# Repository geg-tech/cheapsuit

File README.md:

# *CHEAP SUITS*
A custom Hacker Card in the profile and style of a Bicycle Playing Card.

 <br/>
 <br/>

I've had the idea of a Hack Club playing card for a *long while* (ever since my BakeBuild submission back in April), and with some extra time on my hands and inpsiration from other people submitting hacker cards, I decided to revamp this idea into a hacker card PCB with fully custom art! <br/>
*Featuring cool and shiny graphics! wow!*

this hacker card also doubles as a shameless plug to my insta account lmao

## PCB
### Schematic
 <br/>

### PCB 
 <br/>
 <br/>
 <br/>

## BOM
| part | quantity | price | purpose/name |
| --- | --- | --- | --- |
| 25X48MM_NFC_ANTENNA | 1 | $0.00 (copper layers)| receives power and transmits |
| CL10B224KA8NNNC | 1 | $0.0270 | Assists the power harvester system |
| E6C0805UR | 1 | $0.0050 | 47 ohm resistor to limit power leading to the LED | 
| KT-0805Y | 1 | $0.0625 | 2V red LED that lights up |
| | | |
| PCB | 5 | $2.00 | PCB that holds/wires components together |
| PCBA Total | idk | $15.12 | all the other stuff that comes with PCBA; setup fee, stencil, components, etc. (why is it so damn expensive 🥀) |
| Shipping: $9.97 | Tax: $1.79 | | |
|**Total: $28.85**| ($9.38 with the jlc coupon) | | |
> note: the actual PCBA BOM is located under the production folder

## Firmware
putting this here since the firmware is literally just flashing the NFC chip and uploading with an app <br/>
Command: `A2:03:E1:10:6D:00,A2:04:03:04:D8:00,A2:05:00:00:FE:00` <br/>
Purpose: Will link to my Instagram account (@hunk.egg btw :3)

## extras/inspirations

***fun facts***:
* I drew two alternate back sides to the playing card, being the *Moon* and the *Compass*!
* ^ The *Moon* was inspired off of the background of [Cheap Suits](https://youtu.be/87i0RargAcA) and traditional tarot cards
* ^^ The *Compass* had an original theming for being a *compass* for Highway (get it)

 <br/>

* This project initially had the name of *The Hack* in my head, being named after the Balatro joker of the same name and also matching with *Hack* Club
* ^ i then found out that this was not a poker/cards term, but instead is slang for cliche and unoriginal jokes
* I hid the logos for Highway and Undercity on the back side of the card, as well as the Hack Club flag :3

***inspirations***:
* **Cyberpunk 2077** - Main inspiration behind the cyberpunk/hardcore tech theming
* [**Cheap Suits**](https://youtu.be/87i0RargAcA) by *mekaloton* - Main inspiration for the whole suits/gambling theme; inspired the *Moon* alternate back side; this entire project was named after this song lmao
* **Balatro** - Also a main inspiration for the gambling/suits theme
* **Bicycle Playing Cards** - Main inspiration behind the chosen back side design
* **Highway/Undercity/Hack Club** - (oddly enough) The original source of the cyberpunk aesthetic I wanted with this card; inspired much of the art for the suits, the Undercitified Hack Club logo, and the Highway Stars
* [**Azimuth**](https://www.youtube.com/watch?v=hgSNrjHIIF0) by Knots (YES THIS IS A GEOMETRY DASH LEVEL 🙏😭) - Main inspiration behind the *Compass* alternate back side
* **my calculus teacher** - he got me addicted to poker

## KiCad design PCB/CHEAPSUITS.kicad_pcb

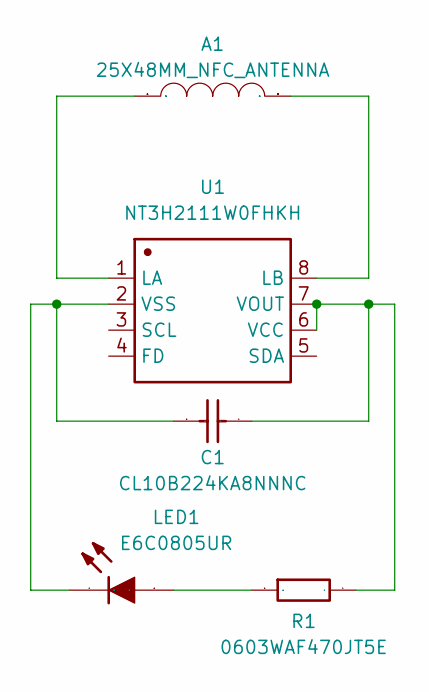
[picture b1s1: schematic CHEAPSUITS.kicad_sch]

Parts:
A1: 25X48MM_NFC_ANTENNA; 25X48MM_NFC_ANTENNA (antenna)
C1: CL10B224KA8NNNC; C0603 (capacitor); Manufacturer Part CL10B224KA8NNNC
LED1: E6C0805UR; LED0805-R-RD (LED); Manufacturer Part KT-0805R
R1: 0603WAF470JT5E; R0603 (resistor); Manufacturer Part 0603WAF470JT5E
U1: NT3H2111W0FHKH; XQFN-8_L1.6-W1.6-P0.50-BL_NT3H2111W0FHKH (NFC); Manufacturer Part NT3H2111W0FHKH

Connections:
unnamed: LED1.1 (A), R1.1
unnamed: C1.1, LED1.2 (K), U1.2 (VSS)
unnamed: A1.P$1, U1.1 (LA)
unnamed: A1.P$2, U1.8 (LB)
unnamed: C1.2, R1.2, U1.6 (VCC), U1.7 (VOUT)

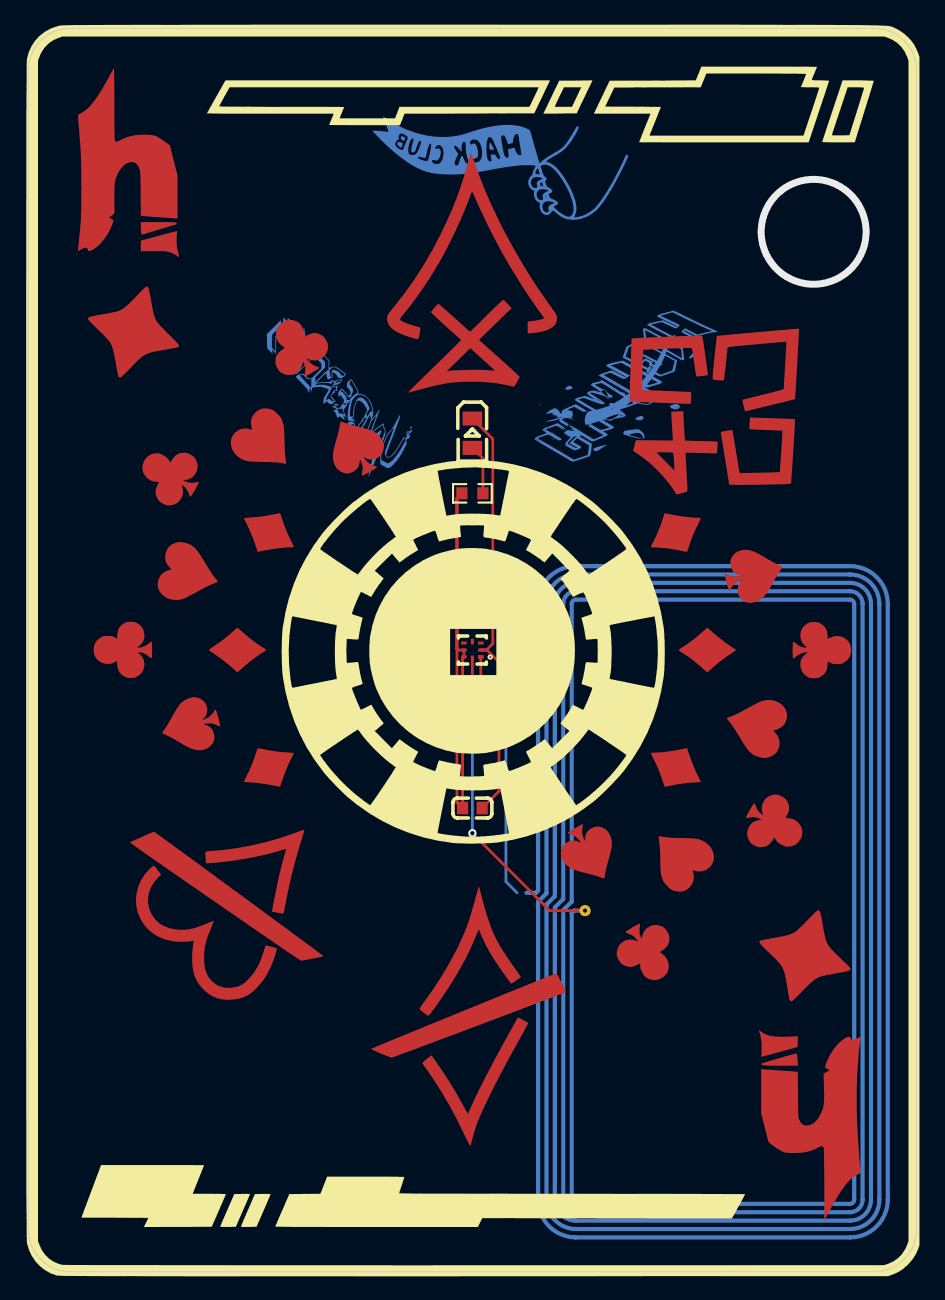
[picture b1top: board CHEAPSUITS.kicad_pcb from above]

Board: 2 copper layers, 63.5 x 88.9 mm, 5 parts (1 on the bottom side), 5 nets.
